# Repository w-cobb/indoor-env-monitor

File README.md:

# Indoor Environment monitor

## Description
This is a project I created to monitor the conditions of my living space. The main inspiration behind this project was to monitor indoor air quality in order to know when
to turn on air purifiers. Since I live in an area that can have poor air quality during the summer months, it could be useful to have localized data for this purpose.

## Specifications
This project was created in VS Code with the ESP IDF v5.5 extension. The hardware used is listed in the table below.

| Component | Description |
| :-------: | :---------: |
| ESP32     | ESP32 C6-Mini-1 |
| BME280    | Adafruit BME280 STEMMA QT board |
| PMS5003   | Adafruit PM2.5 Air Quality Sensor and Breadboard Adapter Kit |

## State of the Project
Everything below this will act as a development blog.

## October 30, 2025

Soldering has begun.

Disclaimer: I am not an electrical engineer and have no formal training in hardware/pcb design. I understand now that some of my passive component choices might not be ideal. In any case, I don't think I will be using 0402 size components unless absolutely necessary. They are TINY! :D

## October 24, 2025
All components have arrived, except for that one silly cable for the BME280 board that I forgot to order from Adafruit.

## October 11, 2025
PCB design is done (for now) and I have ordered the PCBs from OSHPark.

## September 23, 2025
I want to move this project off the breadboard into a more compact design. I decided to start designing a PCB in KiCad.

## September 19, 2025

Breadboarding is complete. Data is being read from both sensors as seen below.

## September 15, 2025
The BME280 is currently communicating over I2C using a custom driver and the ESP IDF HAL.

The next step is to write a custom driver for the PMS5003 sensor utilizing UART.

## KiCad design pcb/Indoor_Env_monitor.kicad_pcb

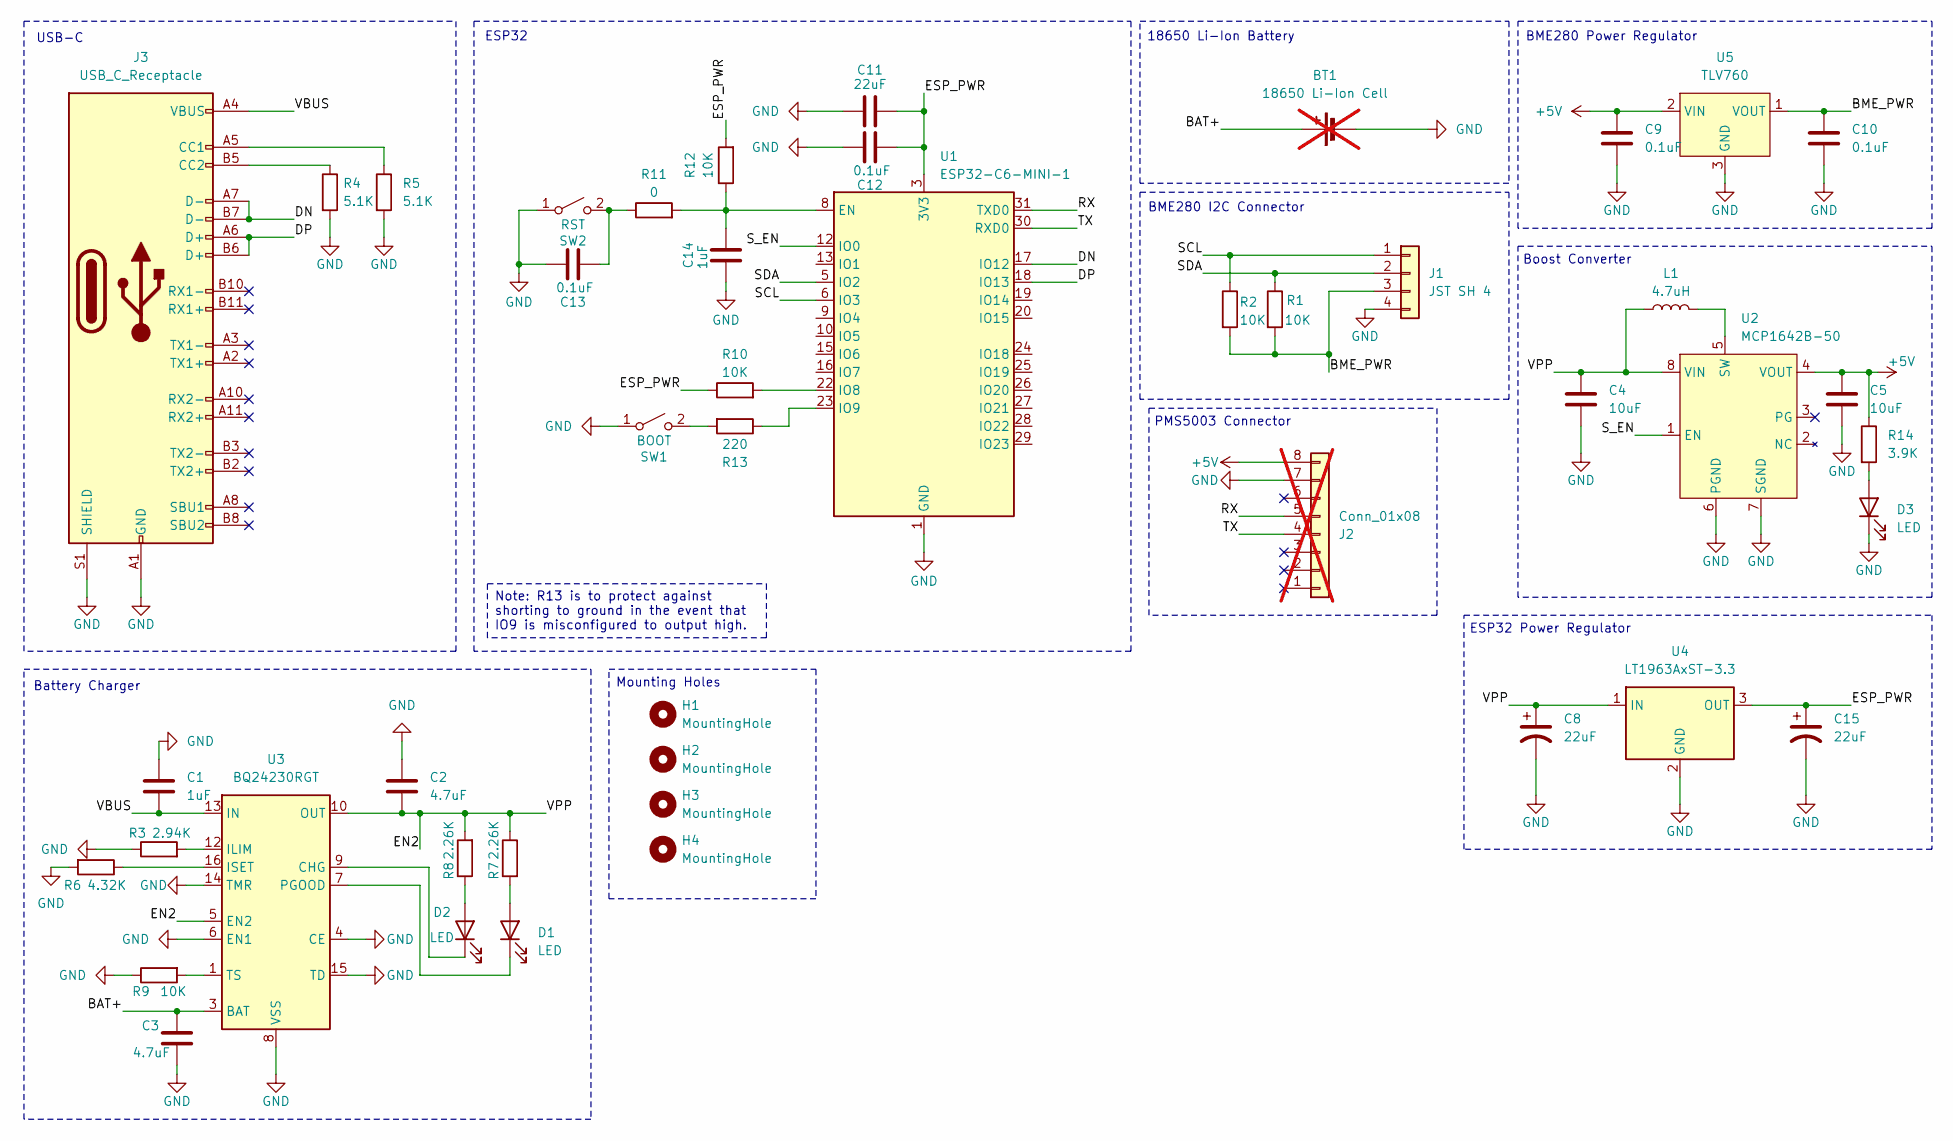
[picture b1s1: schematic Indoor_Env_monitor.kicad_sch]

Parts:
BT1: 18650 Li-Ion Cell; JST_PH_S2B-PH-K_1x02_P2.00mm_Horizontal; not fitted
C1, C14: 1uF; C_0402_1005Metric_Pad0.74x0.62mm_HandSolder
C2, C3: 4.7uF; C_0402_1005Metric_Pad0.74x0.62mm_HandSolder
C4, C5: 10uF; C_0402_1005Metric_Pad0.74x0.62mm_HandSolder
C8, C11, C15: 22uF; C_0402_1005Metric_Pad0.74x0.62mm_HandSolder
C9, C10, C12, C13: 0.1uF; C_0402_1005Metric_Pad0.74x0.62mm_HandSolder
D1, D2, D3: LED; LED_0402_1005Metric_Pad0.77x0.64mm_HandSolder
H1, H2, H3, H4: MountingHole; MountingHole_3.2mm_M3
J1: JST SH 4; JST_SH_BM04B-SRSS-TB_1x04-1MP_P1.00mm_Vertical
J2: Conn_01x08; Molex_PicoBlade_53047-0810_1x08_P1.25mm_Vertical; not fitted
J3: USB_C_Receptacle; USB_C_Receptacle_G-Switch_GT-USB-7010ASV
L1: 4.7uH; L_Coilcraft_LPS4018
R1, R2, R9, R10, R12: 10K; R_0402_1005Metric_Pad0.72x0.64mm_HandSolder
R3: 2.94K; R_0402_1005Metric_Pad0.72x0.64mm_HandSolder
R4, R5: 5.1K; R_0402_1005Metric_Pad0.72x0.64mm_HandSolder
R6: 4.32K; R_0402_1005Metric_Pad0.72x0.64mm_HandSolder
R7, R8: 2.26K; R_0402_1005Metric_Pad0.72x0.64mm_HandSolder
R11: 0; R_0402_1005Metric_Pad0.72x0.64mm_HandSolder
R13: 220; R_0402_1005Metric_Pad0.72x0.64mm_HandSolder
R14: 3.9K; R_0402_1005Metric_Pad0.72x0.64mm_HandSolder
SW1: BOOT; SW_Push_1P1T-SH_NO_CK_KMR2xxG
SW2: RST; SW_Push_1P1T-SH_NO_CK_KMR2xxG
U1: ESP32-C6-MINI-1
U2: MCP1642B-50; MSOP-8_3x3mm_P0.65mm
U3: BQ24230RGT; VQFN-16-1EP_3x3mm_P0.5mm_EP1.68x1.68mm_ThermalVias
U4: LT1963AxST-3.3; SOT-223-3_TabPin2
U5: TLV760; SOT-23_Handsoldering

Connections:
+5V: C5.1, C9.1, J2.8, R14.1, U2.4 (VOUT), U5.2 (VIN)
/BAT+: BT1.1 (+), C3.1, U3.2 (BAT), U3.3 (BAT)
/BME_PWR: C10.1, J1.3, R1.2, R2.2, U5.1 (VOUT)
/DN: J3.A7 (D-), J3.B7 (D-), U1.17 (IO12)
/DP: J3.A6 (D+), J3.B6 (D+), U1.18 (IO13)
/EN2: C2.2, C4.1, C8.1, L1.1, R7.1, R8.2, U2.8 (VIN), U3.5 (EN2), U3.10 (OUT), U3.11 (OUT), U4.1 (IN)
/ESP_PWR: C11.2, C12.2, C15.1, R10.1, R12.2, U1.3 (3V3), U4.3 (OUT)
/RX: J2.5, U1.31 (TXD0)
/SCL: J1.1, R2.1, U1.6 (IO3)
/SDA: J1.2, R1.1, U1.5 (IO2)
/S_EN: U1.12 (IO0), U2.1 (EN)
/TX: J2.4, U1.30 (RXD0)
/VBUS: C1.2, J3.A4 (VBUS), J3.A9 (VBUS), J3.B4 (VBUS), J3.B9 (VBUS), U3.13 (IN)
GND: BT1.2 (-), C1.1, C2.1, C3.2, C4.2, C5.2, C8.2, C9.2, C10.2, C11.1, C12.1, C13.1, C14.2, C15.2, D3.1 (K), J1.4, J2.7, J3.A1 (GND), J3.A12 (GND), J3.B1 (GND), J3.B12 (GND), J3.S1 (SHIELD), R3.1, R4.2, R5.2, R6.2, R9.1, SW1.1 (A), SW2.1 (A), U1.1 (GND), U1.2 (GND), U1.11 (GND), U1.14 (GND), U1.36 (GND), U1.37 (GND), U1.38 (GND), U1.39 (GND), U1.40 (GND), U1.41 (GND), U1.42 (GND), U1.43 (GND), U1.44 (GND), U1.45 (GND), U1.46 (GND), U1.47 (GND), U1.48 (GND), U1.49 (GND), U1.50 (GND), U1.51 (GND), U1.52 (GND), U1.53 (GND), U2.6 (PGND), U2.7 (SGND), U3.4 (CE), U3.6 (EN1), U3.8 (VSS), U3.14 (TMR), U3.15 (TD), U3.17 (VSS), U4.2 (GND), U5.3 (GND)
unnamed: D1.2 (A), R7.2
unnamed: D1.1 (K), U3.7 (PGOOD)
unnamed: D2.2 (A), R8.1
unnamed: D2.1 (K), U3.9 (CHG)
unnamed: D3.2 (A), R14.2
unnamed: J3.A5 (CC1), R5.1
unnamed: J3.B5 (CC2), R4.1
unnamed: R13.2, SW1.2 (B)
unnamed: C13.2, R11.1, SW2.2 (B)
unnamed: C14.1, R11.2, R12.1, U1.8 (EN)
unnamed: R10.2, U1.22 (IO8)
unnamed: R13.1, U1.23 (IO9)
unnamed: L1.2, U2.5 (SW)
unnamed: R3.2, U3.12 (ILIM)
unnamed: R6.1, U3.16 (ISET)
unnamed: R9.2, U3.1 (TS)

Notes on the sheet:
BME280 I2C Connector
Mounting Holes
PMS5003 Connector
ESP32
BME280 Power Regulator
18650 Li-Ion Battery
Battery Charger
Boost Converter
ESP32 Power Regulator
USB-C
Note: R13 is to protect against shorting to ground in the event that IO9 is misconfigured to output high.

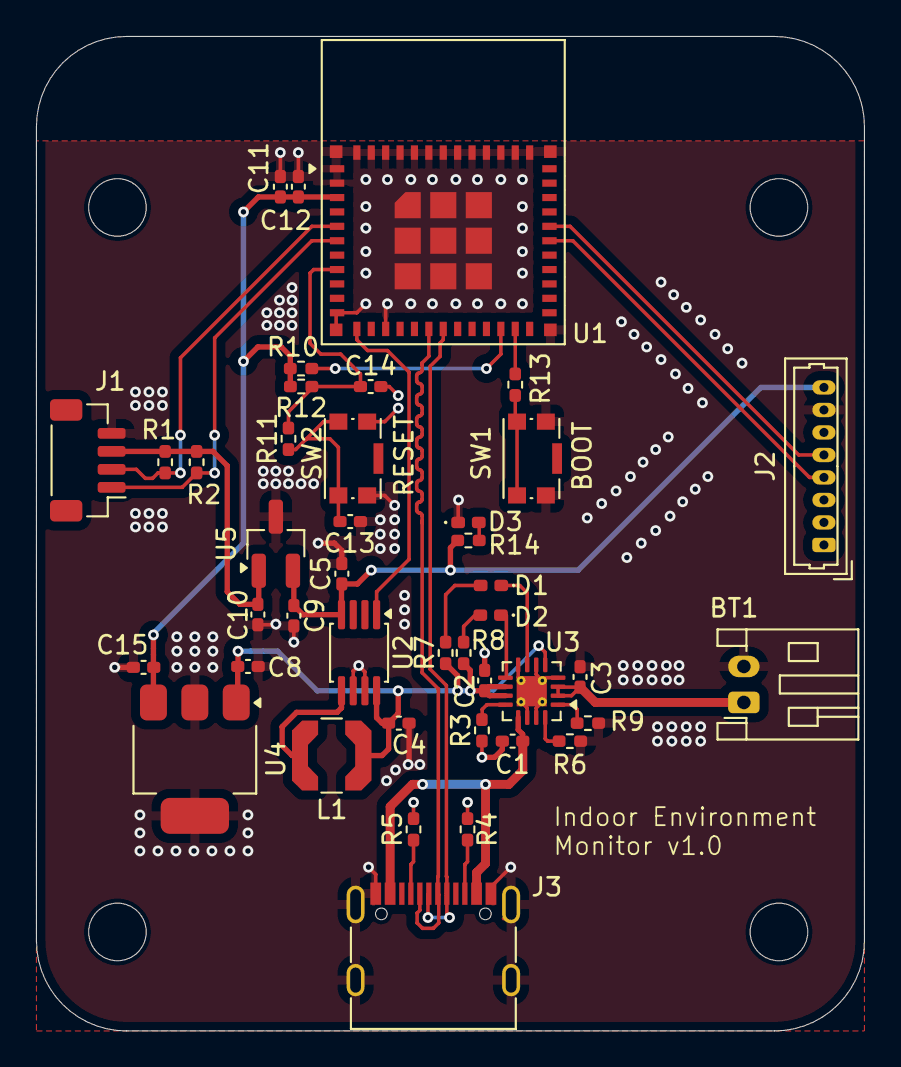
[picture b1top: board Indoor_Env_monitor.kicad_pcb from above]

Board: 2 copper layers, 46.0 x 55.2 mm, 46 parts (0 on the bottom side), 30 nets.

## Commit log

2025-09-16 Reverted code back to C
2025-09-16 Fixed writeConfig overwriting config every loop
2025-09-23 Add code to read data over UART from PMS5003 sensor
2025-09-23 Add configuration attributes for configuring UART
2025-09-23 Read and print data from PMS5003
2025-09-23 Added docs folder and example image
2025-09-23 Added pcb folder, KiCad files, and entry to gitignore for KiCad backups
2025-10-14 Created the schematic and PCB
2025-10-18 Little change
2025-10-31 Add images
2025-10-31 Revise README with project details and blog updates
    Updated project description and specifications, added development blog entries.
